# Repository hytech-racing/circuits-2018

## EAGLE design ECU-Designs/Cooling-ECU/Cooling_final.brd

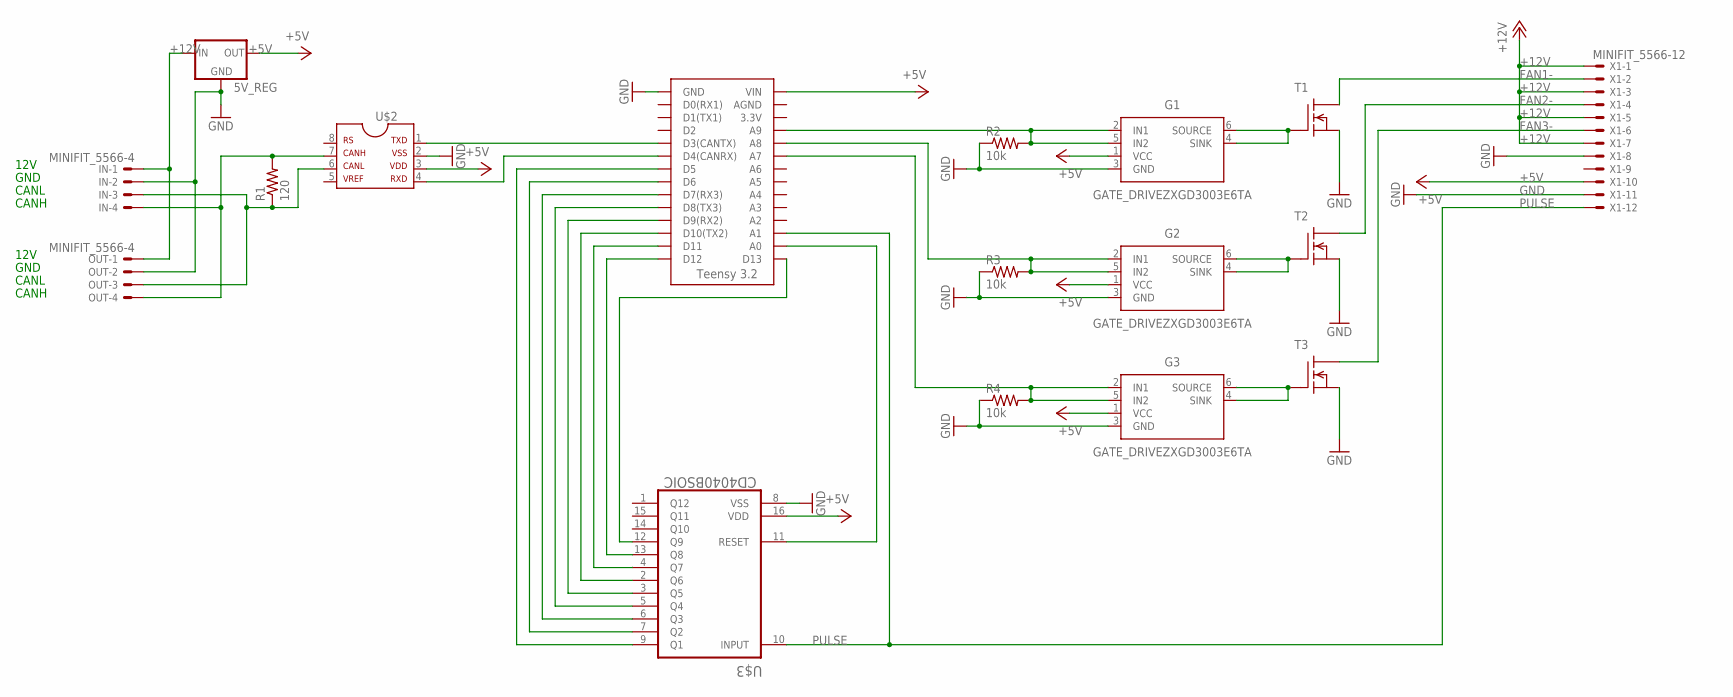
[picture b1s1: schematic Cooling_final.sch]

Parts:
5V_REG: 5V_REGULATOR_LM340-NLM340MPX-5.0/NOPB; SOT223
G1, G2, G3: GATE_DRIVEZXGD3003E6TA; SOT23-6
IN: MINIFIT_5566-4
OUT: MINIFIT_5566-4
R1: 120; 0805
R2, R3, R4: 10k; 0805
T1, T2, T3: N-CHANNEL_MOSFETGENERIC; TO-220-SINK
U$1: TEENSY_3.2_SIMPLE
U$2: MCP2551; SOIC-08
U$3: CD4040BSOIC; SOIC-16
X1: MINIFIT_5566-12

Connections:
+5V: 5V_REG.2 (OUT), 5V_REG.4 (OUT), G1.1 (VCC), G2.1 (VCC), G3.1 (VCC), U$1.VIN, U$2.3, U$3.16 (VDD), X1.10
+12V: 5V_REG.3 (IN), IN.1, OUT.1, X1.1, X1.3, X1.5, X1.7
FAN1-: T1.2 (D), X1.2
FAN2-: T2.2 (D), X1.4
FAN3-: T3.2 (D), X1.6
GND: 5V_REG.1 (GND), G1.3 (GND), G2.3 (GND), G3.3 (GND), IN.2, OUT.2, R2.1, R3.1, R4.1, T1.3 (S), T2.3 (S), T3.3 (S), U$1.GND, U$2.2, U$3.8 (VSS), X1.8, X1.11
unnamed: G1.4 (SINK), G1.6 (SOURCE), T1.1 (G)
unnamed: U$1.D3(CANTX), U$2.1
unnamed: U$1.D4(CANRX), U$2.4
unnamed: G2.4 (SINK), G2.6 (SOURCE), T2.1 (G)
unnamed: G3.4 (SINK), G3.6 (SOURCE), T3.1 (G)
unnamed: IN.3, OUT.3, R1.1
unnamed: IN.4, OUT.4, R1.2, U$2.7
unnamed: U$1.D5, U$3.9 (Q1)
unnamed: U$1.D6, U$3.7 (Q2)
unnamed: U$1.D7(RX3), U$3.6 (Q3)
unnamed: U$1.D8(TX3), U$3.5 (Q4)
unnamed: U$1.D9(RX2), U$3.3 (Q5)
unnamed: U$1.D10(TX2), U$3.2 (Q6)
unnamed: G1.2 (IN1), G1.5 (IN2), R2.2, U$1.A9
unnamed: G2.2 (IN1), G2.5 (IN2), R3.2, U$1.A8
unnamed: G3.2 (IN1), G3.5 (IN2), R4.2, U$1.A7
unnamed: U$1.D11, U$3.4 (Q7)
unnamed: U$1.D12, U$3.13 (Q8)
unnamed: U$1.A0, U$3.11 (RESET)
unnamed: U$1.D13, U$3.12 (Q9)
PULSE: U$1.A1, U$3.10 (INPUT), X1.12

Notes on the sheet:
12V
GND
CANL
CANH

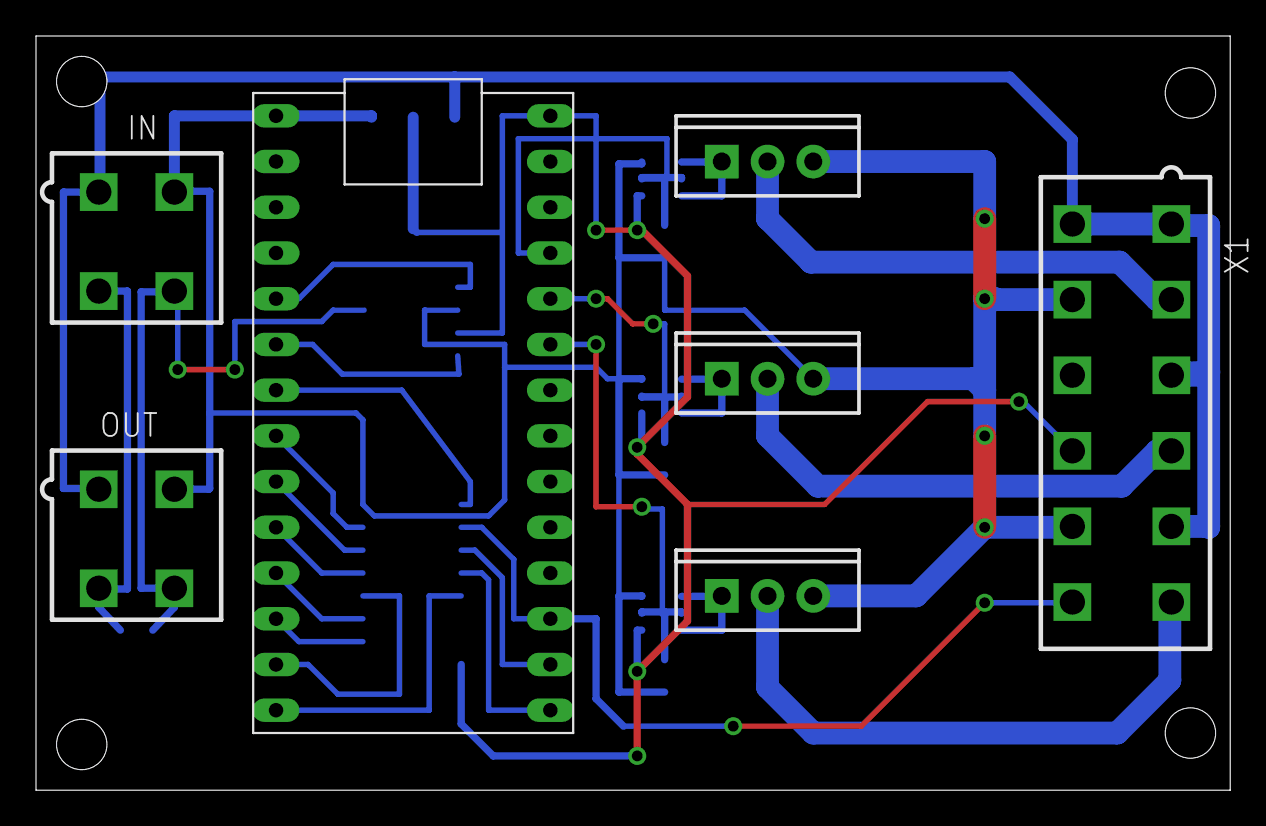
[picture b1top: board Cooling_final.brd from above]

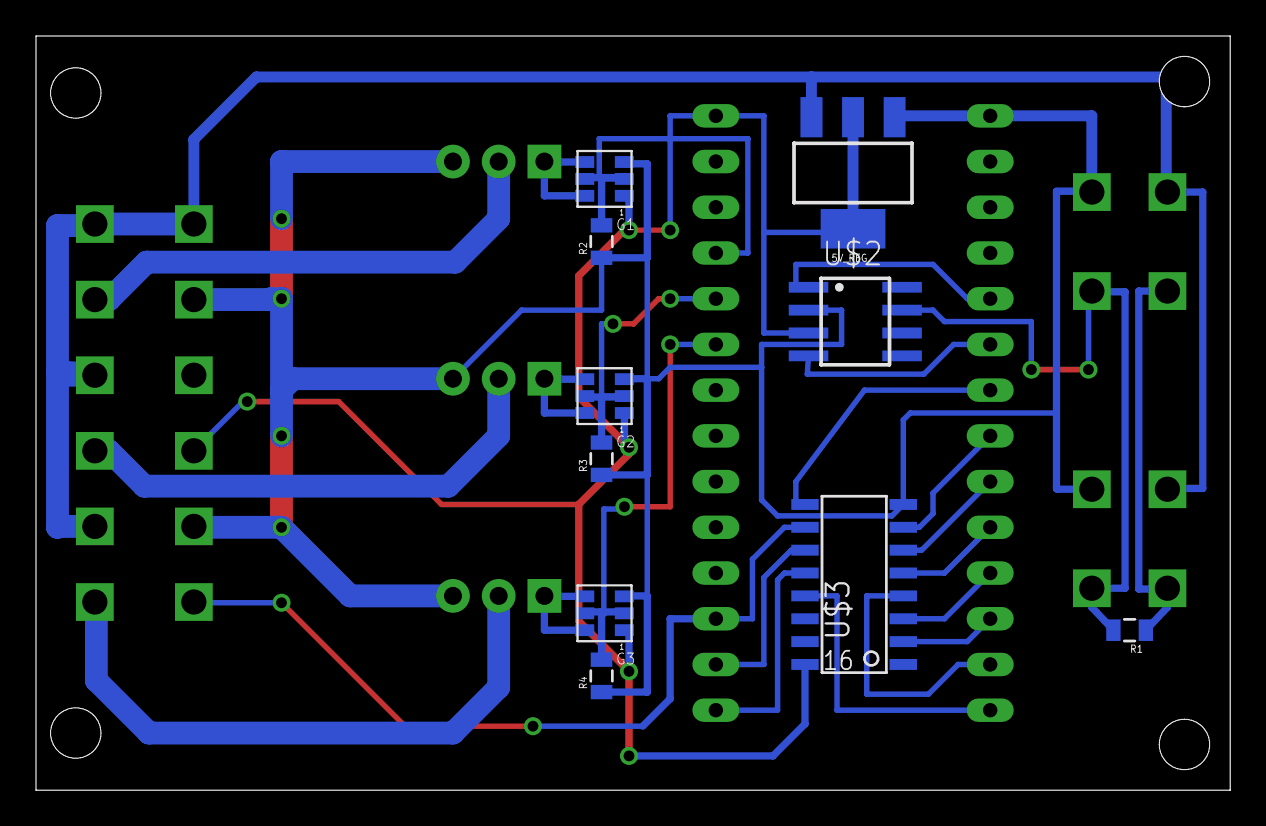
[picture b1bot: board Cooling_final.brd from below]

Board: 2 copper layers, 66.3 x 41.9 mm, 17 parts (10 on the bottom side), 27 nets.

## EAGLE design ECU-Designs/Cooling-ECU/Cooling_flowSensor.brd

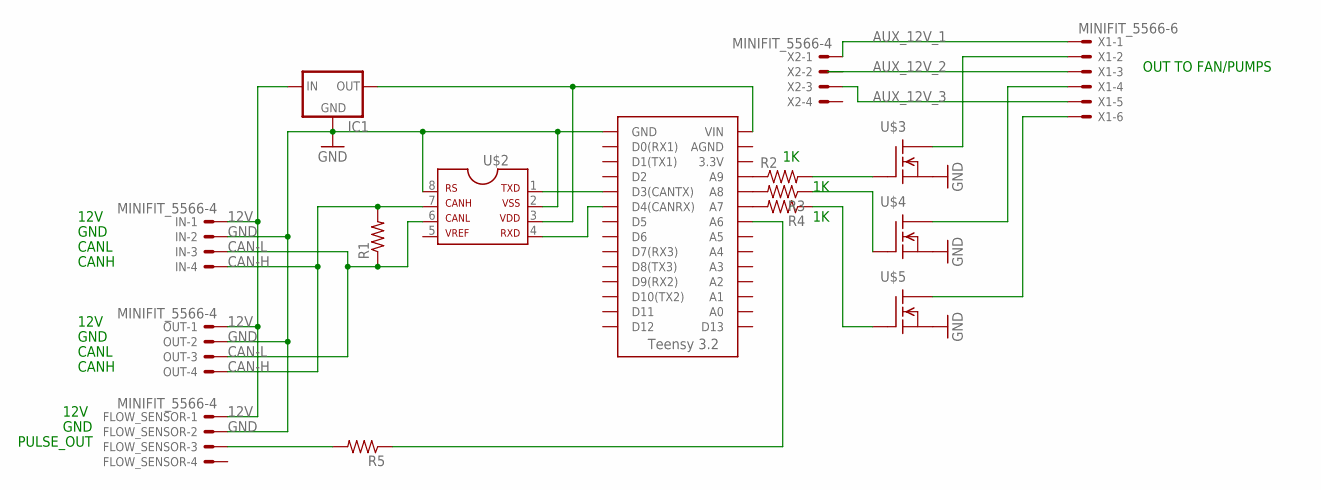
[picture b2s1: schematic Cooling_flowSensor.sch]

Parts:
FLOW_SENSOR: MINIFIT_5566-4
IC1: 5V_REGULATOR_LM340-NLM340MPX-5.0/NOPB; SOT223
IN: MINIFIT_5566-4
OUT: MINIFIT_5566-4
R1, R2, R3, R4, R5: RESISTOR0805-RES; 0805
U$1: TEENSY_3.2_SIMPLE
U$2: MCP2551SOIC; SOIC08
U$3, U$4, U$5: PSMN011_MOSFET; SOT669
X1: MINIFIT_5566-6
X2: MINIFIT_5566-4

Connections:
5V: IC1.2 (OUT), IC1.4 (OUT), U$1.VIN, U$2.3
12V: FLOW_SENSOR.1, IC1.3 (IN), IN.1, OUT.1
AUX_12V_1: X1.1, X2.1
AUX_12V_2: X1.3
AUX_12V_3: X1.5, X2.3
CAN-H: IN.4, OUT.4, R1.2, U$2.7
CAN-L: IN.3, OUT.3, R1.1
GND: FLOW_SENSOR.2, IC1.1 (GND), IN.2, OUT.2, U$1.GND, U$2.2, U$2.8, U$3.1 (S), U$3.2 (S), U$3.3 (S), U$4.1 (S), U$4.2 (S), U$4.3 (S), U$5.1 (S), U$5.2 (S), U$5.3 (S)
unnamed: R2.1, U$1.A9
unnamed: U$1.D3(CANTX), U$2.1
unnamed: U$1.D4(CANRX), U$2.4
unnamed: R3.2, U$1.A8
unnamed: R4.2, U$1.A7
unnamed: FLOW_SENSOR.3, R5.2
unnamed: R2.2, U$3.4 (G)
unnamed: R5.1, U$1.A6
unnamed: R3.1, U$4.4 (G)
unnamed: R4.1, U$5.4 (G)
unnamed: U$4.MB (D), U$4.MB2 (D), X1.4
unnamed: U$5.MB (D), U$5.MB2 (D), X1.6
unnamed: U$3.MB (D), U$3.MB2 (D), X1.2

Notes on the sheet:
12V
GND
CANL
CANH
PULSE_OUT
OUT TO FAN/PUMPS

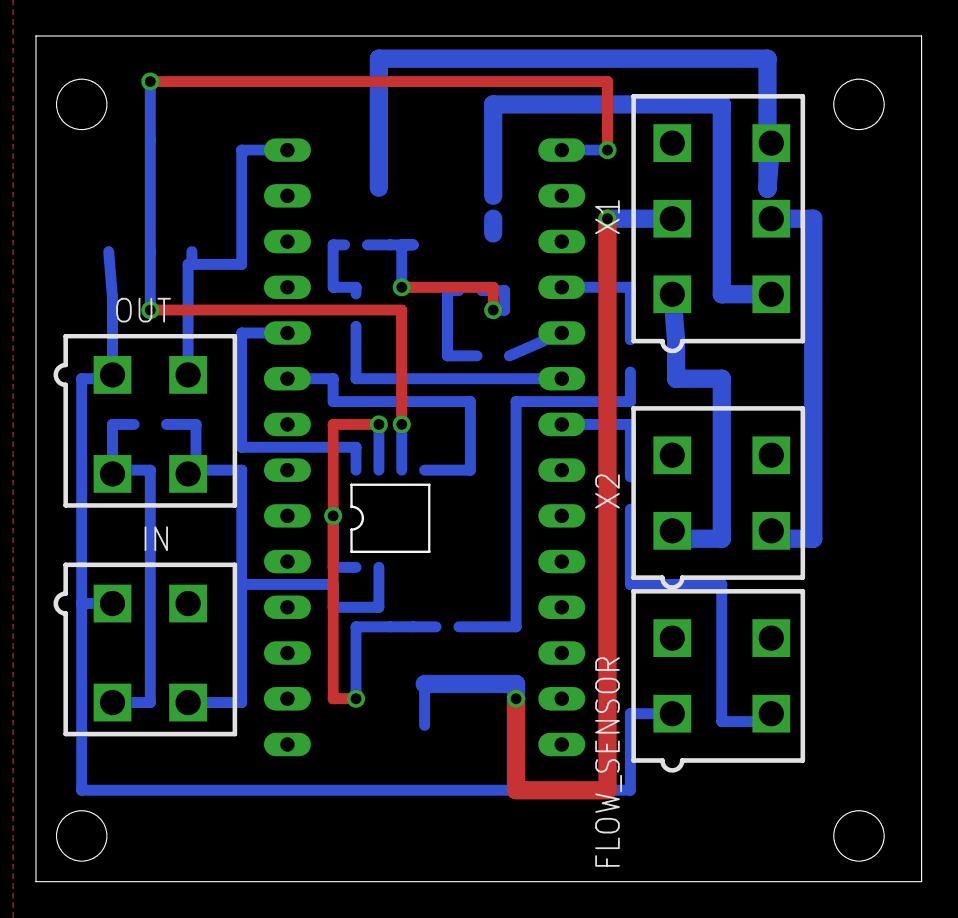
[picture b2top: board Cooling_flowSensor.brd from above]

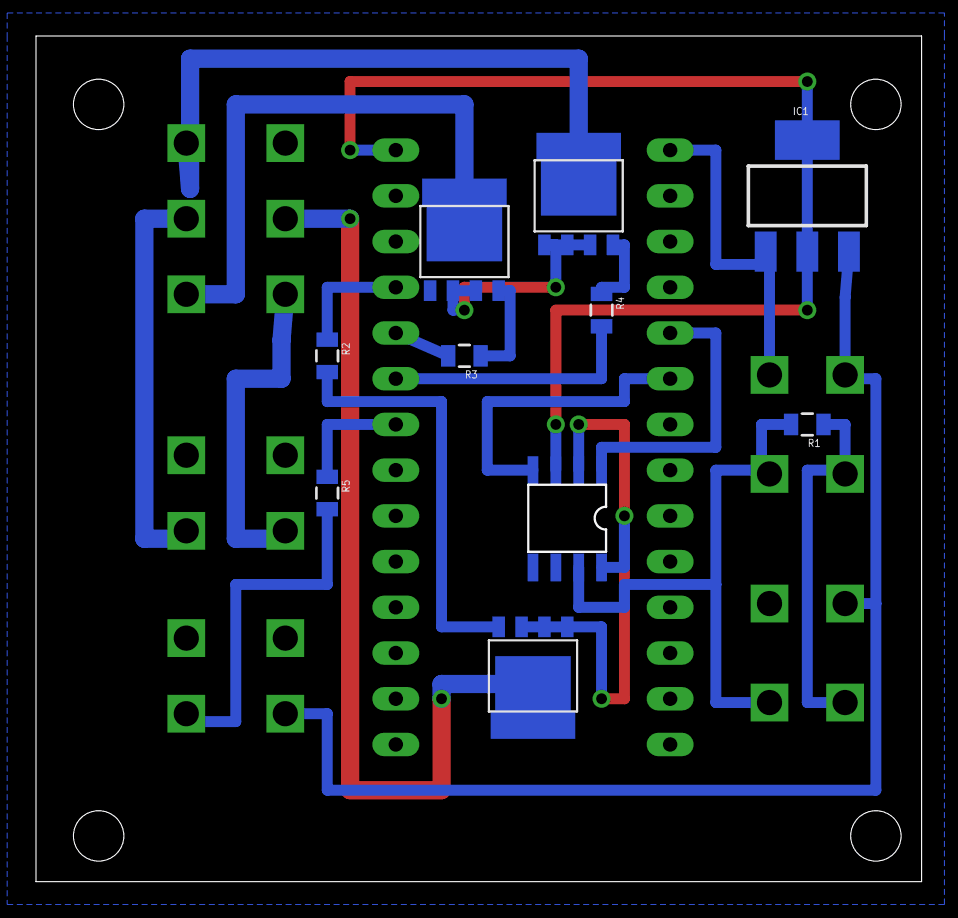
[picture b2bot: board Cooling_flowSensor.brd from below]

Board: 2 copper layers, 49.2 x 47.0 mm, 16 parts (10 on the bottom side), 20 nets.

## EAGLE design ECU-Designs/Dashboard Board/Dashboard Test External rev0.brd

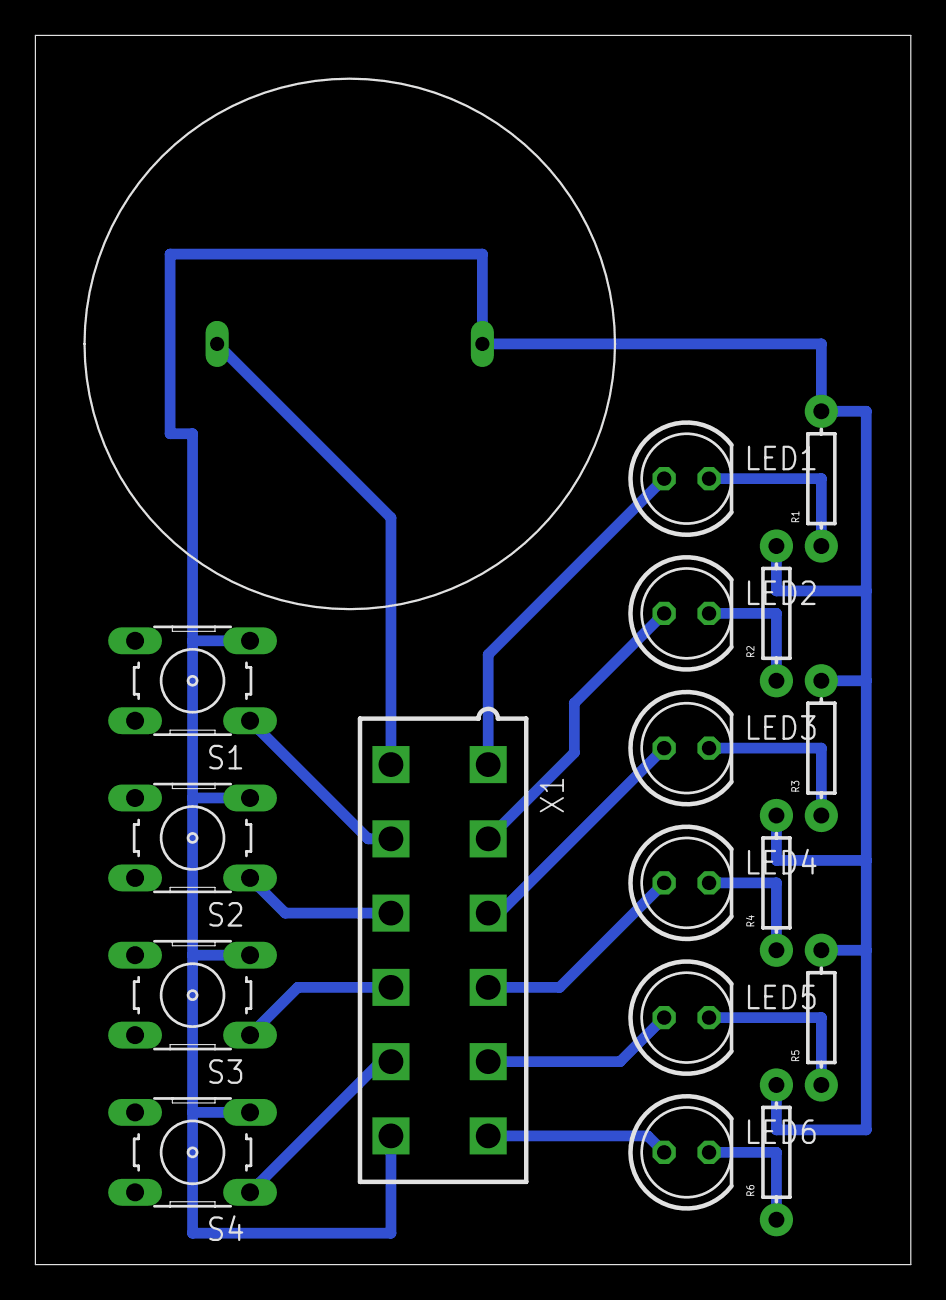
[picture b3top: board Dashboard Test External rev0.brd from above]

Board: 2 copper layers, 49.5 x 69.5 mm, 18 parts (0 on the bottom side), 18 nets.

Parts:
LED1, LED2, LED3, LED4, LED5, LED6: LED-5MM
R1, R2, R3, R4, R5, R6: AXIAL-0.3EZ
S1, S2, S3, S4: B3F-10XX
U$1: AI-3035-TWT-3V-R
X1: MINIFIT_5566-12

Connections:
GND: R1.P$2, R2.P$2, R3.P$2, R4.P$2, R5.P$2, R6.P$2, S1.3, S2.3, S3.3, S4.3, U$1.P$2, X1.12
unnamed: S1.1, X1.8
unnamed: S2.1, X1.9
unnamed: S3.1, X1.10
unnamed: S4.1, X1.11
unnamed: U$1.P$1, X1.7
unnamed: LED6.A, X1.6
unnamed: LED5.A, X1.5
unnamed: LED4.A, X1.4
unnamed: LED3.A, X1.3
unnamed: LED2.A, X1.2
unnamed: LED1.A, X1.1
unnamed: LED1.K, R1.P$1
unnamed: LED2.K, R2.P$1
unnamed: LED3.K, R3.P$1
unnamed: LED4.K, R4.P$1
unnamed: LED5.K, R5.P$1
unnamed: LED6.K, R6.P$1

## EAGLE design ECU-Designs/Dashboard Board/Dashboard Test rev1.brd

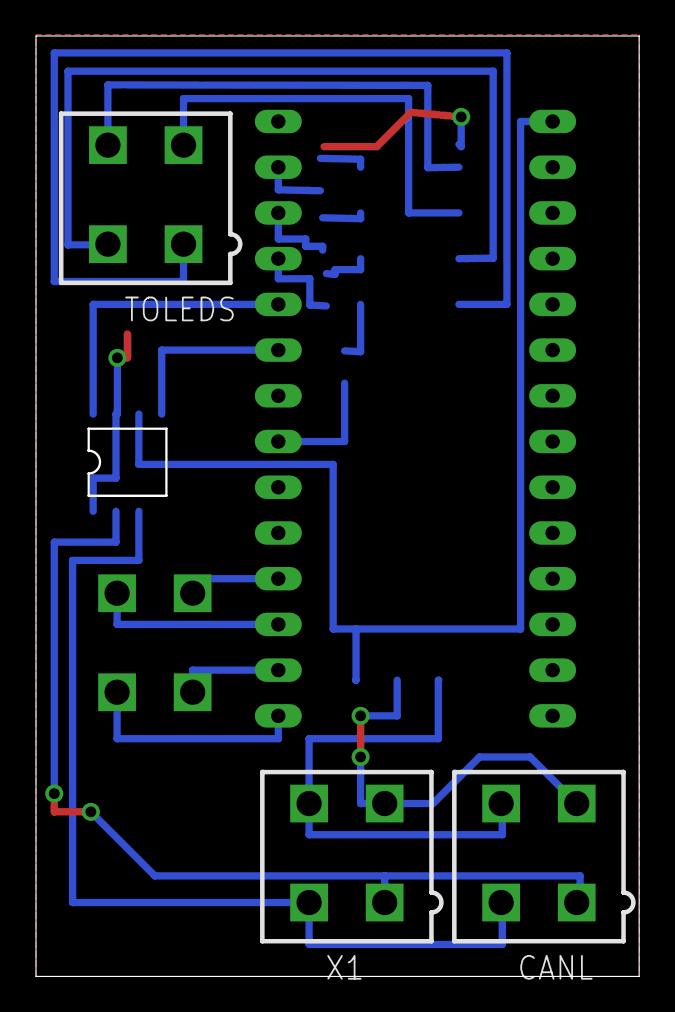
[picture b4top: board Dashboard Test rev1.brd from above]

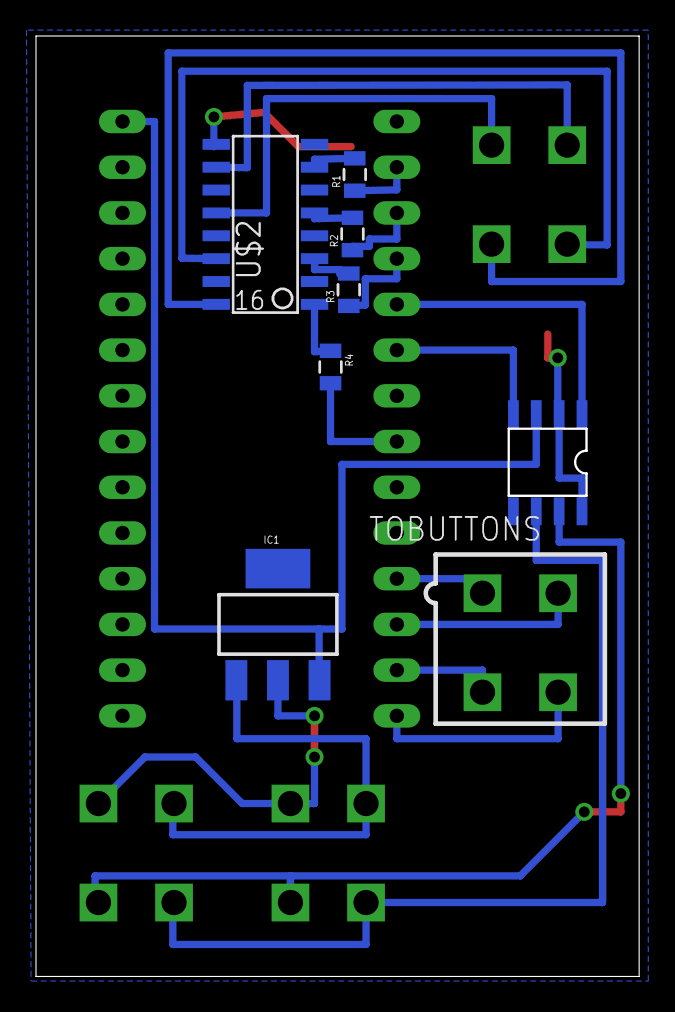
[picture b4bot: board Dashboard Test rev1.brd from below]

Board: 2 copper layers, 33.5 x 52.2 mm, 12 parts (8 on the bottom side), 23 nets.

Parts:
CAN: MCP2551SOIC; SOIC08
CANL: MINIFIT_5566-4
IC1: SOT223
R1, R2, R3, R4: 220; 0805
TOBUTTONS: MINIFIT_5566-4
TOLEDS: MINIFIT_5566-4
U$1: TEENSY_3.2_SIMPLE
U$2: OPTOCOUPLER_QUAD_TLP291-4; SO-16
X1: MINIFIT_5566-4

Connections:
12VSUPPLY: CANL.4, IC1.1, X1.4
BUTTON_BOOST: TOBUTTONS.2, U$1.D10(TX2)
BUTTON_SELECT: TOBUTTONS.1, U$1.D9(RX2)
BUTTON_START: TOBUTTONS.4, U$1.D12
BUTTON_TOGGLE: TOBUTTONS.3, U$1.D11
CANH: CAN.7, CANL.1, X1.1
CANL: CAN.6, CANL.2, X1.2
GND: CAN.2, CAN.8, CANL.3, IC1.2, IC1.4, U$2.2, U$2.4, U$2.6, U$2.8, U$2.9, U$2.11, U$2.13, U$2.15, X1.3
LED_BMS: TOLEDS.3, U$2.12
LED_IMD: TOLEDS.2, U$2.14
LED_POWER: TOLEDS.1, U$2.16
unnamed: R1.1, U$1.D0(RX1)
unnamed: CAN.1, U$1.D3(CANTX)
unnamed: CAN.4, U$1.D4(CANRX)
unnamed: R2.1, U$1.D1(TX1)
unnamed: R3.1, U$1.D2
unnamed: R4.1, U$2.1
unnamed: R4.2, U$1.D6
unnamed: R1.2, U$2.7
unnamed: R2.2, U$2.5
unnamed: R3.2, U$2.3
unnamed: CAN.3, IC1.3, U$1.VIN
RTDS_POWER: TOLEDS.4, U$2.10

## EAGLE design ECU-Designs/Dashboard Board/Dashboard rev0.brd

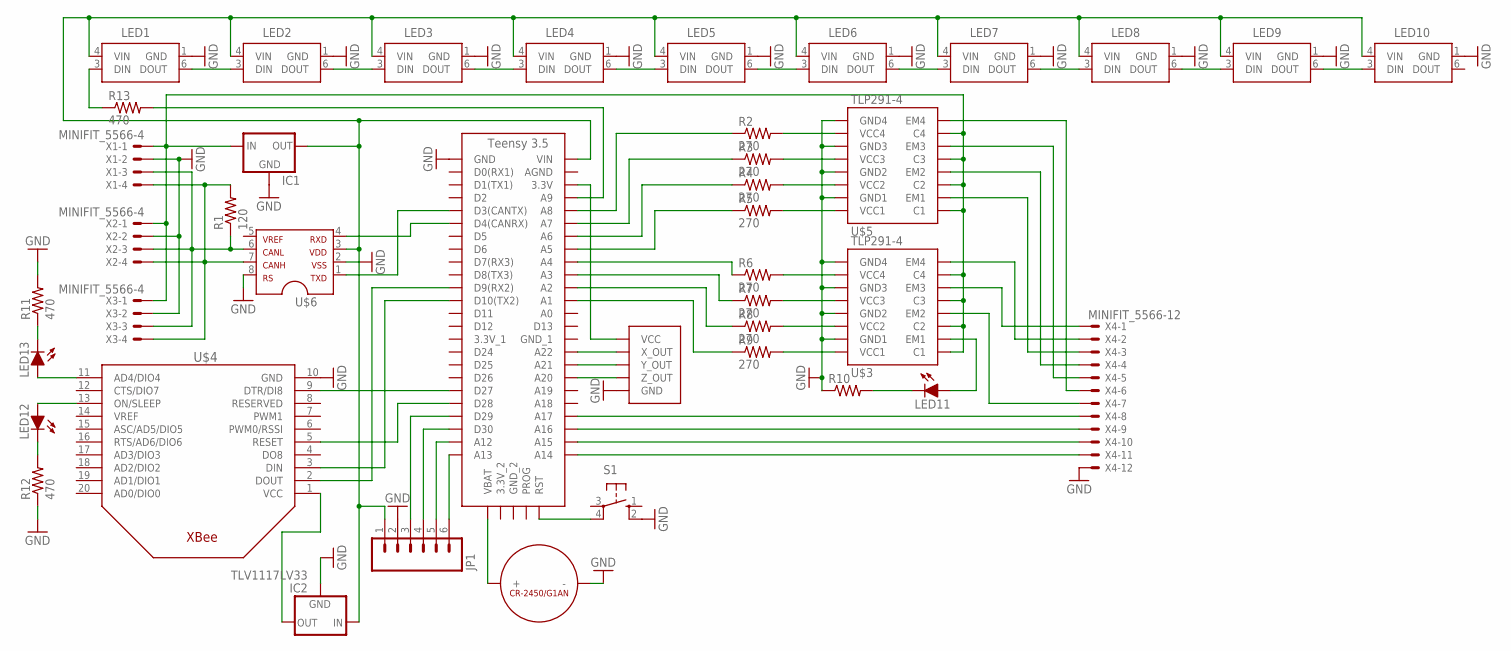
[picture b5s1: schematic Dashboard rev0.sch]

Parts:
IC1: 5VREG_L7805_HOR; TO-220-H
IC2: TLV1117LV33; SOT223
JP1: M06; 1X06
LED1, LED2, LED3, LED4, LED5, LED6, LED7, LED8, LED9, LED10: WS2812B5050; RGBLED5050
LED11, LED12, LED13: LED-0805; LED-805
R1: 120; 0805
R2, R3, R4, R5, R6, R7, R8, R9: 270; 0805
R10: RESISTOR0805-RES; 0805
R11, R12, R13: 470; 0805
S1: BTN_10-XX; B3F-10XX
U$1: TEENSY_3.5_SIMPLE_RTC
U$2: CR-2450/G1AN
U$3, U$5: TLP291-4; SOIC-16
U$4: XBEE
U$6: MCP2551; SOIC-08
U$7: ADXL335
X1, X2, X3: MINIFIT_5566-4
X4: MINIFIT_5566-12

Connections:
GND: IC1.2 (GND), IC2.1 (GND), JP1.2, LED1.1 (GND), LED2.1 (GND), LED3.1 (GND), LED4.1 (GND), LED5.1 (GND), LED6.1 (GND), LED7.1 (GND), LED8.1 (GND), LED9.1 (GND), LED10.1 (GND), R10.1, R11.2, R12.1, S1.2 (S1), U$1.GND, U$2.-, U$3.2 (GND1), U$3.4 (GND2), U$3.6 (GND3), U$3.8 (GND4), U$4.10 (GND), U$5.2 (GND1), U$5.4 (GND2), U$5.6 (GND3), U$5.8 (GND4), U$6.2, U$6.8, U$7.GND, X1.2, X2.2, X3.2, X4.12
unnamed: U$1.VBAT, U$2.+_0 (+), U$2.+_1 (+)
unnamed: R2.2, U$5.7 (VCC4)
unnamed: LED1.6 (DOUT), LED2.3 (DIN)
unnamed: LED2.6 (DOUT), LED3.3 (DIN)
unnamed: LED3.6 (DOUT), LED4.3 (DIN)
unnamed: LED4.6 (DOUT), LED5.3 (DIN)
unnamed: LED5.6 (DOUT), LED6.3 (DIN)
unnamed: LED6.6 (DOUT), LED7.3 (DIN)
unnamed: LED7.6 (DOUT), LED8.3 (DIN)
unnamed: LED8.6 (DOUT), LED9.3 (DIN)
unnamed: LED9.6 (DOUT), LED10.3 (DIN)
unnamed: R3.2, U$5.5 (VCC3)
unnamed: U$1.D3(CANTX), U$6.1
unnamed: IC1.1 (IN), U$3.10 (C4), U$3.12 (C3), U$3.14 (C2), U$3.16 (C1), U$5.10 (C4), U$5.12 (C3), U$5.14 (C2), U$5.16 (C1), X1.1, X2.1, X3.1
unnamed: U$1.D4(CANRX), U$6.4
unnamed: R1.1, U$6.6, X1.3, X2.3, X3.3
unnamed: R1.2, U$6.7, X1.4, X2.4, X3.4
unnamed: LED12.A, U$4.13 (ON/SLEEP)
unnamed: R13.2, U$1.A9
unnamed: R2.1, U$1.A8
unnamed: R3.1, U$1.A7
unnamed: R4.1, U$1.A6
unnamed: R5.1, U$1.A5
unnamed: R6.1, U$1.A4
unnamed: R7.1, U$1.A3
unnamed: R8.1, U$1.A2
unnamed: R9.1, U$1.A1
unnamed: R4.2, U$5.3 (VCC2)
unnamed: R5.2, U$5.1 (VCC1)
unnamed: R6.2, U$3.7 (VCC4)
unnamed: R7.2, U$3.5 (VCC3)
unnamed: R8.2, U$3.3 (VCC2)
unnamed: R9.2, U$3.1 (VCC1)
unnamed: U$1.3.3V, U$7.VCC
unnamed: U$1.A22, U$7.X_OUT
unnamed: U$1.A21, U$7.Y_OUT
unnamed: U$1.A20, U$7.Z_OUT
unnamed: S1.4 (P1), U$1.RST
unnamed: U$1.D28, U$4.5 (RESET)
unnamed: U$1.A14, X4.11
unnamed: U$1.A16, X4.9
unnamed: U$5.9 (EM4), X4.6
unnamed: U$5.11 (EM3), X4.5
unnamed: U$5.13 (EM2), X4.4
unnamed: U$5.15 (EM1), X4.3
unnamed: U$3.9 (EM4), X4.2
unnamed: U$3.11 (EM3), X4.1
unnamed: U$3.13 (EM2), X4.7
unnamed: LED11.A, U$3.15 (EM1)
unnamed: U$1.A17, X4.8
unnamed: U$1.A15, X4.10
unnamed: U$1.D9(RX2), U$4.2 (DOUT)
unnamed: U$1.D10(TX2), U$4.3 (DIN)
unnamed: U$1.D27, U$4.9 (DTR/DI8)
unnamed: LED11.C, R10.2
unnamed: LED13.A, U$4.11 (AD4/DIO4)
unnamed: LED13.C, R11.1
unnamed: LED12.C, R12.2
unnamed: IC1.3 (OUT), IC2.3 (IN), JP1.1, LED1.4 (VIN), LED2.4 (VIN), LED3.4 (VIN), LED4.4 (VIN), LED5.4 (VIN), LED6.4 (VIN), LED7.4 (VIN), LED8.4 (VIN), LED9.4 (VIN), LED10.4 (VIN), U$1.VIN, U$6.3
unnamed: JP1.5, U$1.A12
unnamed: JP1.4, U$1.D30
unnamed: JP1.3, U$1.D29
unnamed: JP1.6, U$1.A13
unnamed: LED1.3 (DIN), R13.1
VCC: IC2.2 (OUT), IC2.4 (OUT), U$4.1 (VCC)

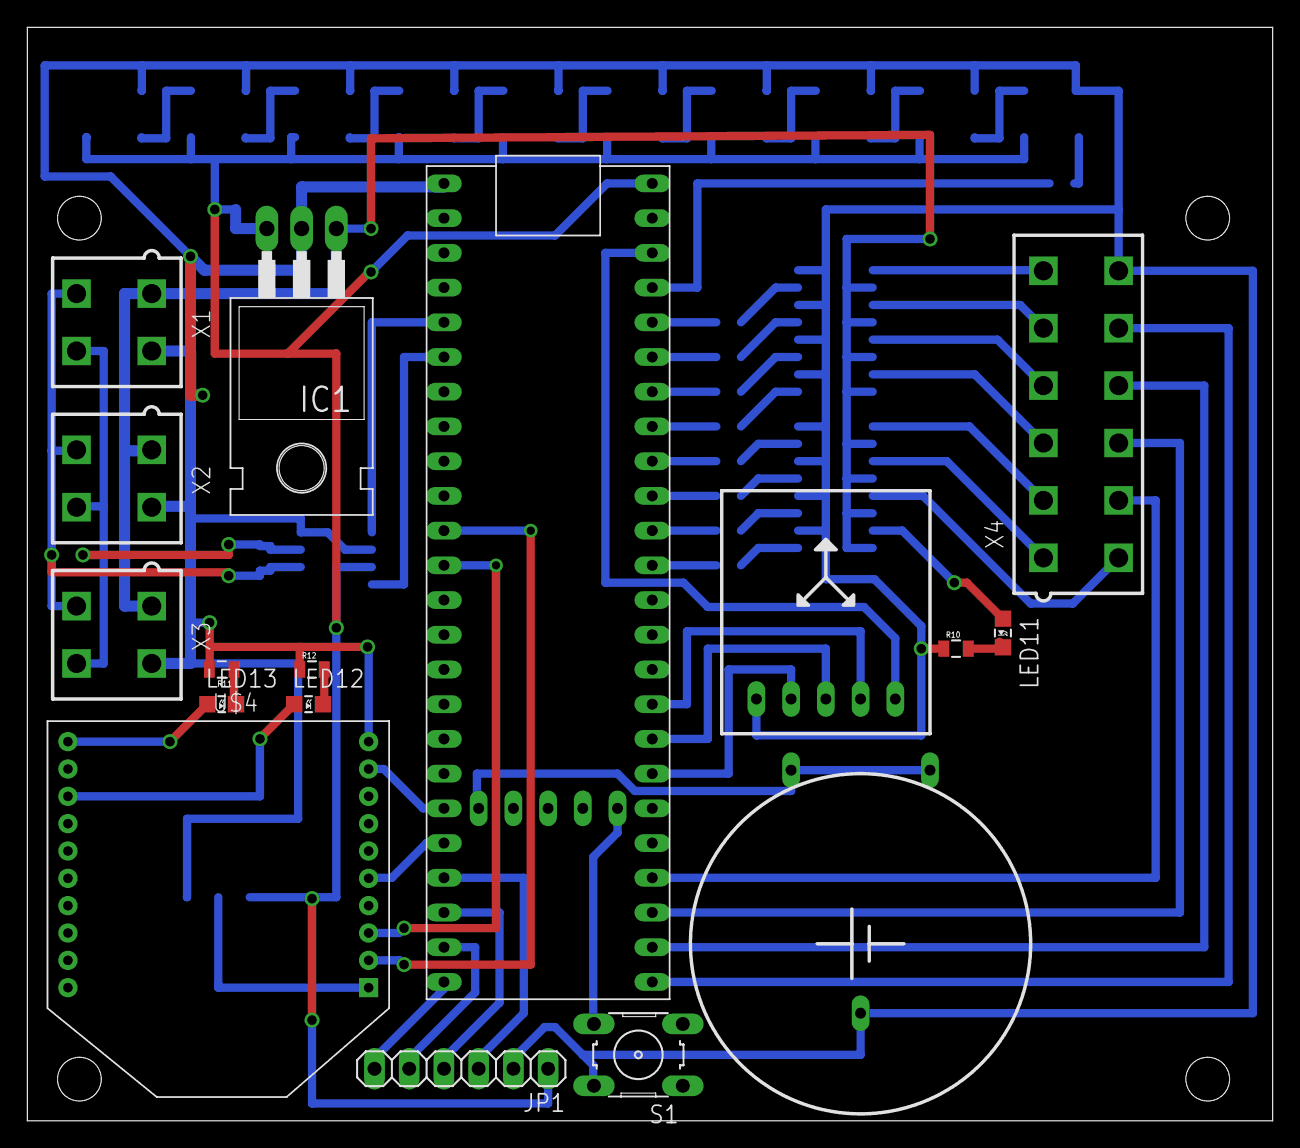
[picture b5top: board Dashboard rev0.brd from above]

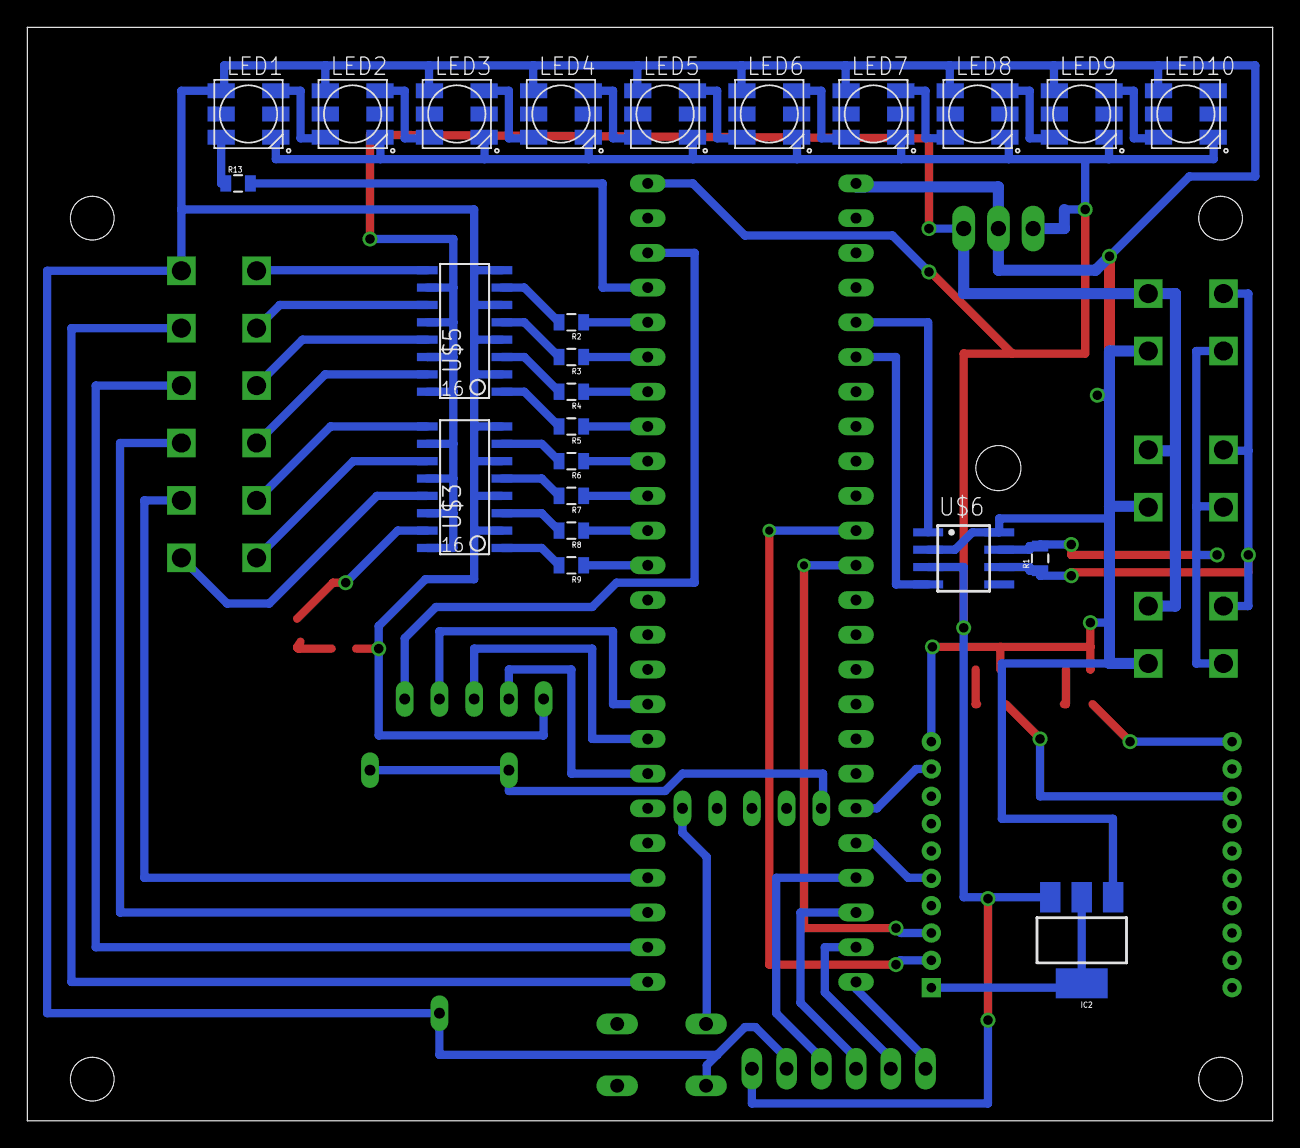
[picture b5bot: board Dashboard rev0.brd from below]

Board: 2 copper layers, 91.1 x 80.0 mm, 41 parts (24 on the bottom side), 66 nets.

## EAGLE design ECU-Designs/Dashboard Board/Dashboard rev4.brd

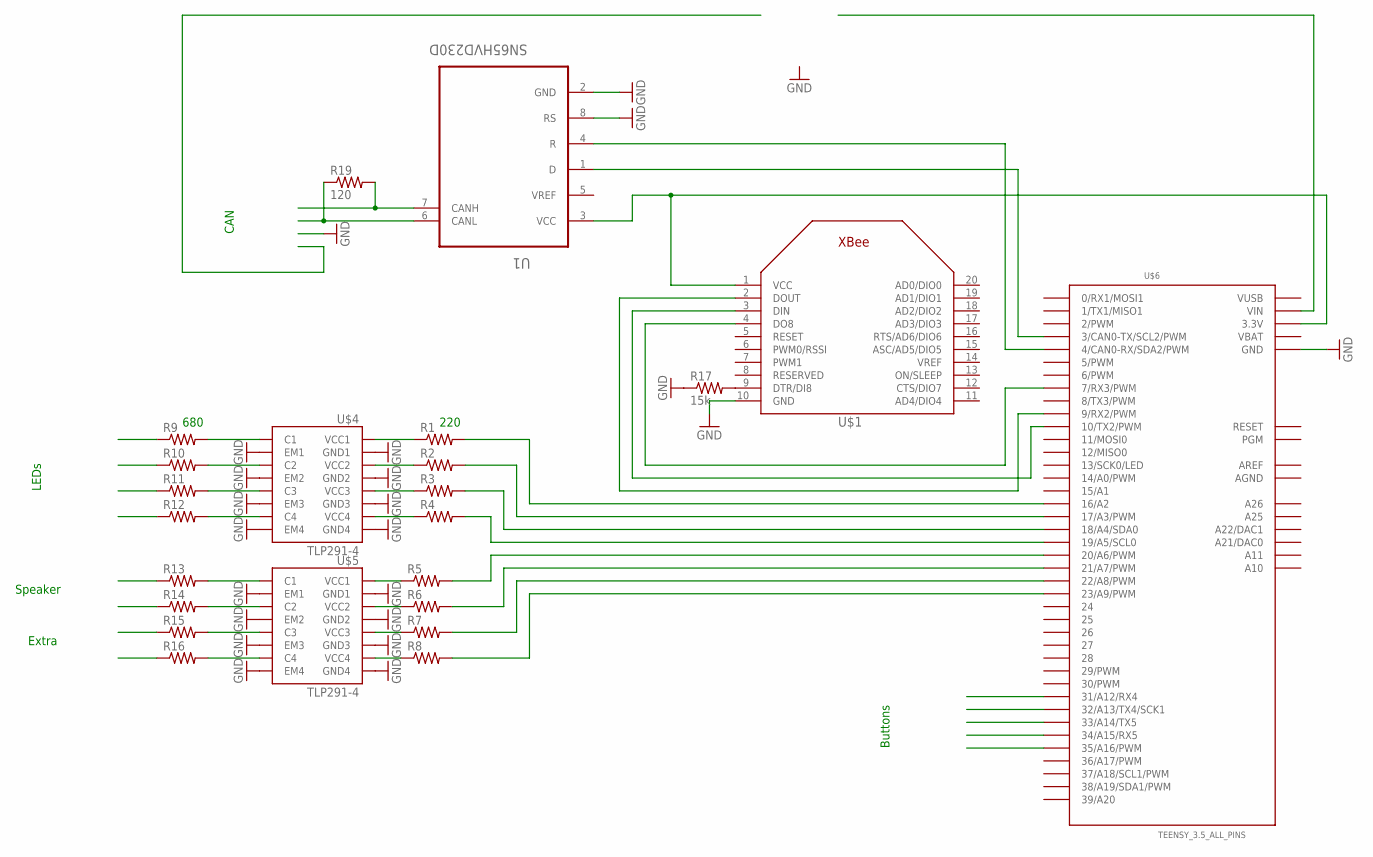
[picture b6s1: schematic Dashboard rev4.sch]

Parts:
R1, R2, R3, R4, R5, R6, R7, R8, R9, R10, R11, R12, R13, R14, R15, R16: RESISTORAXIAL-0.3; AXIAL-0.3
R17: 15k; AXIAL-0.3
R19: 120; AXIAL-0.3
U1: SN65HVD230D; SOIC127P600X175-8N
U$1: XBEE
U$4, U$5: TLP291-4; SOIC-16
U$6: TEENSY_3.5_ALL_PINS

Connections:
AGND: U$6.AGND
AREF: U$6.AREF
GND: R17.P$1 (1), U1.2 (GND), U1.8 (RS), U$1.10 (GND), U$4.2 (GND1), U$4.4 (GND2), U$4.6 (GND3), U$4.8 (GND4), U$4.9 (EM4), U$4.11 (EM3), U$4.13 (EM2), U$4.15 (EM1), U$5.2 (GND1), U$5.4 (GND2), U$5.6 (GND3), U$5.8 (GND4), U$5.9 (EM4), U$5.11 (EM3), U$5.13 (EM2), U$5.15 (EM1), U$6.GND, U$6.GND1 (GND), U$6.GND3 (GND), U$6.GND4 (GND), U$6.GND6 (GND)
unnamed: U$1.2 (DOUT), U$6.9 (9/RX2/PWM)
unnamed: R1.P$1 (1), U$4.1 (VCC1)
unnamed: R2.P$1 (1), U$4.3 (VCC2)
unnamed: R3.P$1 (1), U$4.5 (VCC3)
unnamed: U$1.3 (DIN), U$6.10 (10/TX2/PWM)
unnamed: U$1.4 (DO8), U$6.7 (7/RX3/PWM)
unnamed: R4.P$1 (1), U$4.7 (VCC4)
unnamed: R5.P$1 (1), U$5.1 (VCC1)
unnamed: R17.P$2 (2), U$1.9 (DTR/DI8)
unnamed: R6.P$1 (1), U$5.3 (VCC2)
unnamed: R7.P$1 (1), U$5.5 (VCC3)
unnamed: R8.P$1 (1), U$5.7 (VCC4)
unnamed: U1.1 (D), U$6.3 (3/CAN0-TX/SCL2/PWM)
unnamed: R9.P$2 (2), U$4.16 (C1)
unnamed: R10.P$2 (2), U$4.14 (C2)
unnamed: R11.P$2 (2), U$4.12 (C3)
unnamed: R12.P$2 (2), U$4.10 (C4)
unnamed: R13.P$2 (2), U$5.16 (C1)
unnamed: R14.P$2 (2), U$5.14 (C2)
unnamed: R15.P$2 (2), U$5.12 (C3)
unnamed: R16.P$2 (2), U$5.10 (C4)
unnamed: U1.4 (R), U$6.4 (4/CAN0-RX/SDA2/PWM)
unnamed: R19.P$2 (2), U1.7 (CANH)
unnamed: R1.P$2 (2), U$6.16/A2
unnamed: R2.P$2 (2), U$6.17/A3 (17/A3/PWM)
unnamed: R3.P$2 (2), U$6.18/A4 (18/A4/SDA0)
unnamed: R19.P$1 (1), U1.6 (CANL)
unnamed: R4.P$2 (2), U$6.19/A5 (19/A5/SCL0)
unnamed: R5.P$2 (2), U$6.20/A6 (20/A6/PWM)
unnamed: R6.P$2 (2), U$6.21/A7 (21/A7/PWM)
unnamed: R7.P$2 (2), U$6.22/A8 (22/A8/PWM)
unnamed: R8.P$2 (2), U$6.23/A9 (23/A9/PWM)
VBAT: U$6.VBAT
VCC: U1.3 (VCC), U$1.1 (VCC), U$6.3.3V, U$6.3.3V3 (3.3V), U$6.3.3V4 (3.3V)
VUSB: U$6.VUSB

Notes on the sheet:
680
220
Buttons
Speaker
Extra
LEDs
CAN

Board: 2 copper layers, 23 parts (2 on the bottom side), 34 nets, no tracks yet.

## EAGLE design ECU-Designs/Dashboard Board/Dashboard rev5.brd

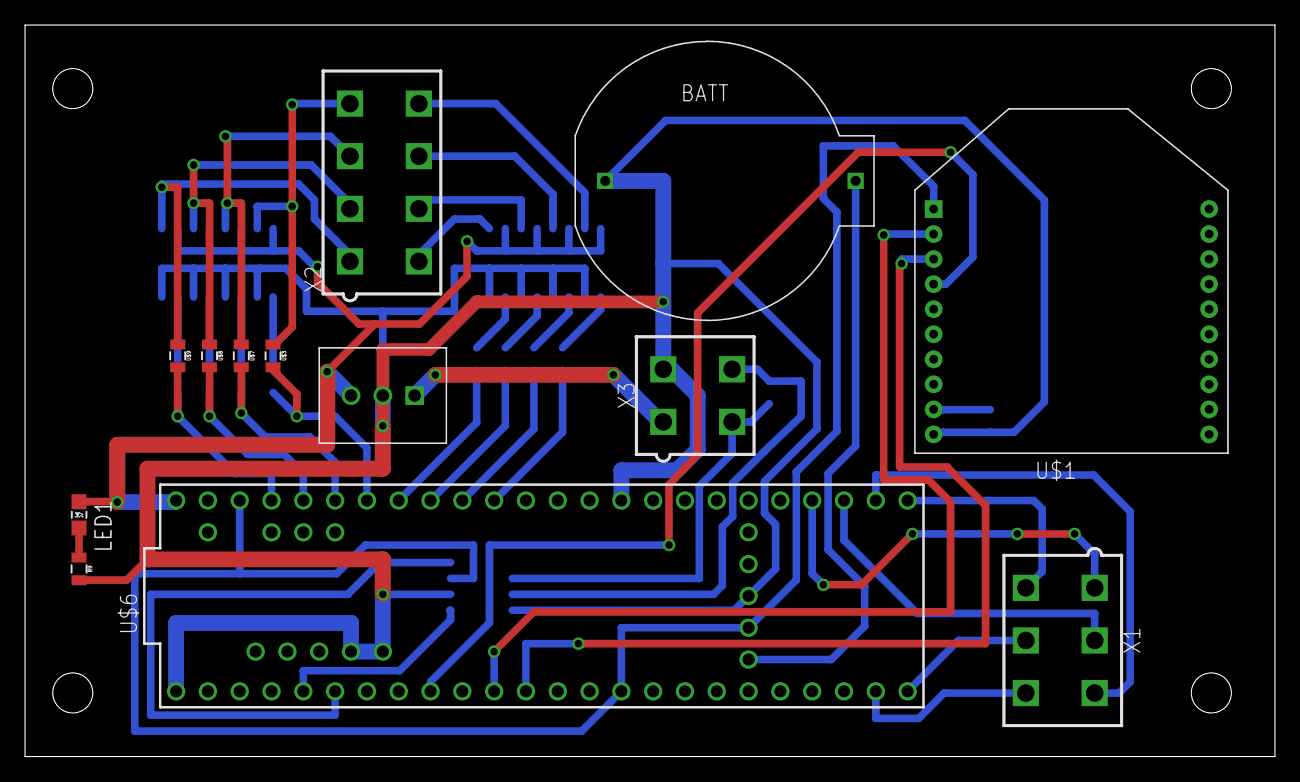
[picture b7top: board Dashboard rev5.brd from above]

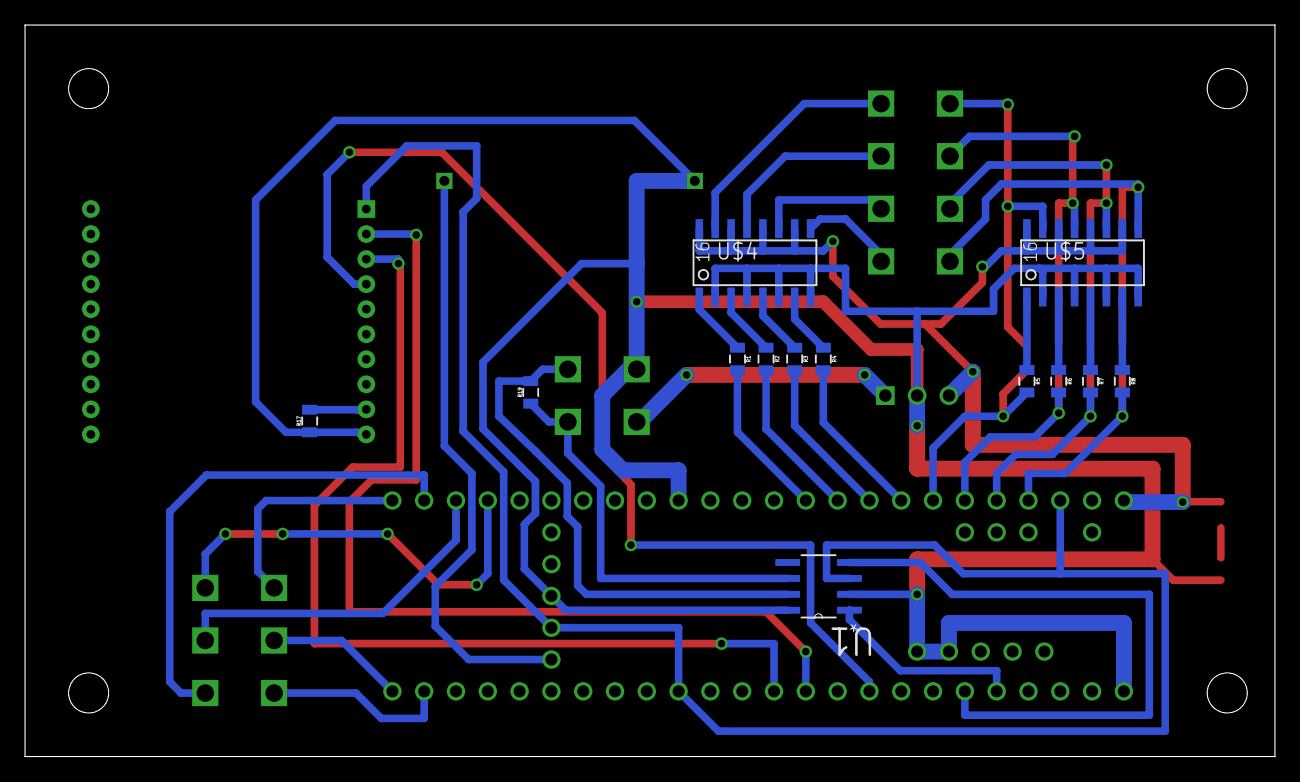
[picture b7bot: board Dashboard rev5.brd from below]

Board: 2 copper layers, 99.8 x 58.4 mm, 26 parts (13 on the bottom side), 44 nets.

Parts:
BATT: COIN-CELL-HOLDER
IC1: TO-220-SPACED
LED1: LED-805
R1, R2, R3, R4, R5, R6, R7, R8: 220; 0805
R9: 0805
R17: 15k; 0805
R19: 120; 0805
U1: SN65HVD230D; SOIC127P600X175-8N
U$1: XBEE
U$3, U$7, U$8, U$9: JUMPER; 0805
U$4, U$5: TLP291-4; SOIC-16
U$6: TEENSY_3.5_ALL_PINS
X1: CONNECTOR-6; MINIFIT_5566-6
X2: CONNECTOR-8; MINIFIT_5566-8
X3: CONNECTOR-4; MINIFIT_5566-4

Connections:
+5V: IC1.3, LED1.A, U$4.10, U$4.12, U$4.14, U$4.16, U$5.10, U$5.12, U$5.14, U$5.16, U$6.VIN
GND: BATT.GND, IC1.2, R9.2, R17.1, U1.2, U1.8, U$1.10, U$4.2, U$4.4, U$4.6, U$4.8, U$5.2, U$5.4, U$5.6, U$5.8, U$6.GND, U$6.GND1, U$6.GND3, U$6.GND4, U$6.GND6, X3.2
unnamed: U$4.15, X2.8
unnamed: U$1.2, U$6.9
unnamed: U$4.13, X2.7
unnamed: U$4.11, X2.6
unnamed: R1.1, U$4.1
unnamed: U$6.36/A17, X1.1
unnamed: R2.1, U$4.3
unnamed: R3.1, U$4.5
unnamed: U$1.3, U$6.10
unnamed: U$1.4, U$6.7
unnamed: R4.1, U$4.7
unnamed: R5.1, U$5.1
unnamed: R17.2, U$1.9
unnamed: R6.1, U$5.3
unnamed: R7.1, U$5.5
unnamed: R8.1, U$5.7
unnamed: U$6.31/A12, X1.6
unnamed: LED1.C, R9.1
unnamed: U$6.32/A13, X1.5
unnamed: U$6.33/A14, X1.4
unnamed: U$6.34/A15, X1.3
unnamed: U$6.35/A16, X1.2
unnamed: BATT.VDD, U$6.VBAT
unnamed: U1.1, U$6.3
unnamed: U$4.9, X2.5
unnamed: U$3.1, U$5.15, X2.4
unnamed: U$5.13, U$7.1, X2.3
unnamed: U$5.11, U$8.1, X2.2
unnamed: U$5.9, U$9.1, X2.1
unnamed: U1.4, U$6.4
unnamed: R19.2, U1.7, X3.4
unnamed: R1.2, U$6.16/A2
unnamed: R2.2, U$6.17/A3
unnamed: R3.2, U$6.18/A4
unnamed: R19.1, U1.6, X3.3
unnamed: IC1.1, X3.1
unnamed: R4.2, U$6.19/A5
unnamed: R5.2, U$3.2, U$6.20/A6
unnamed: R6.2, U$6.21/A7, U$7.2
unnamed: R7.2, U$6.22/A8, U$8.2
unnamed: R8.2, U$6.23/A9, U$9.2
VCC: U1.3, U$1.1, U$6.3.3V, U$6.3.3V3, U$6.3.3V4
